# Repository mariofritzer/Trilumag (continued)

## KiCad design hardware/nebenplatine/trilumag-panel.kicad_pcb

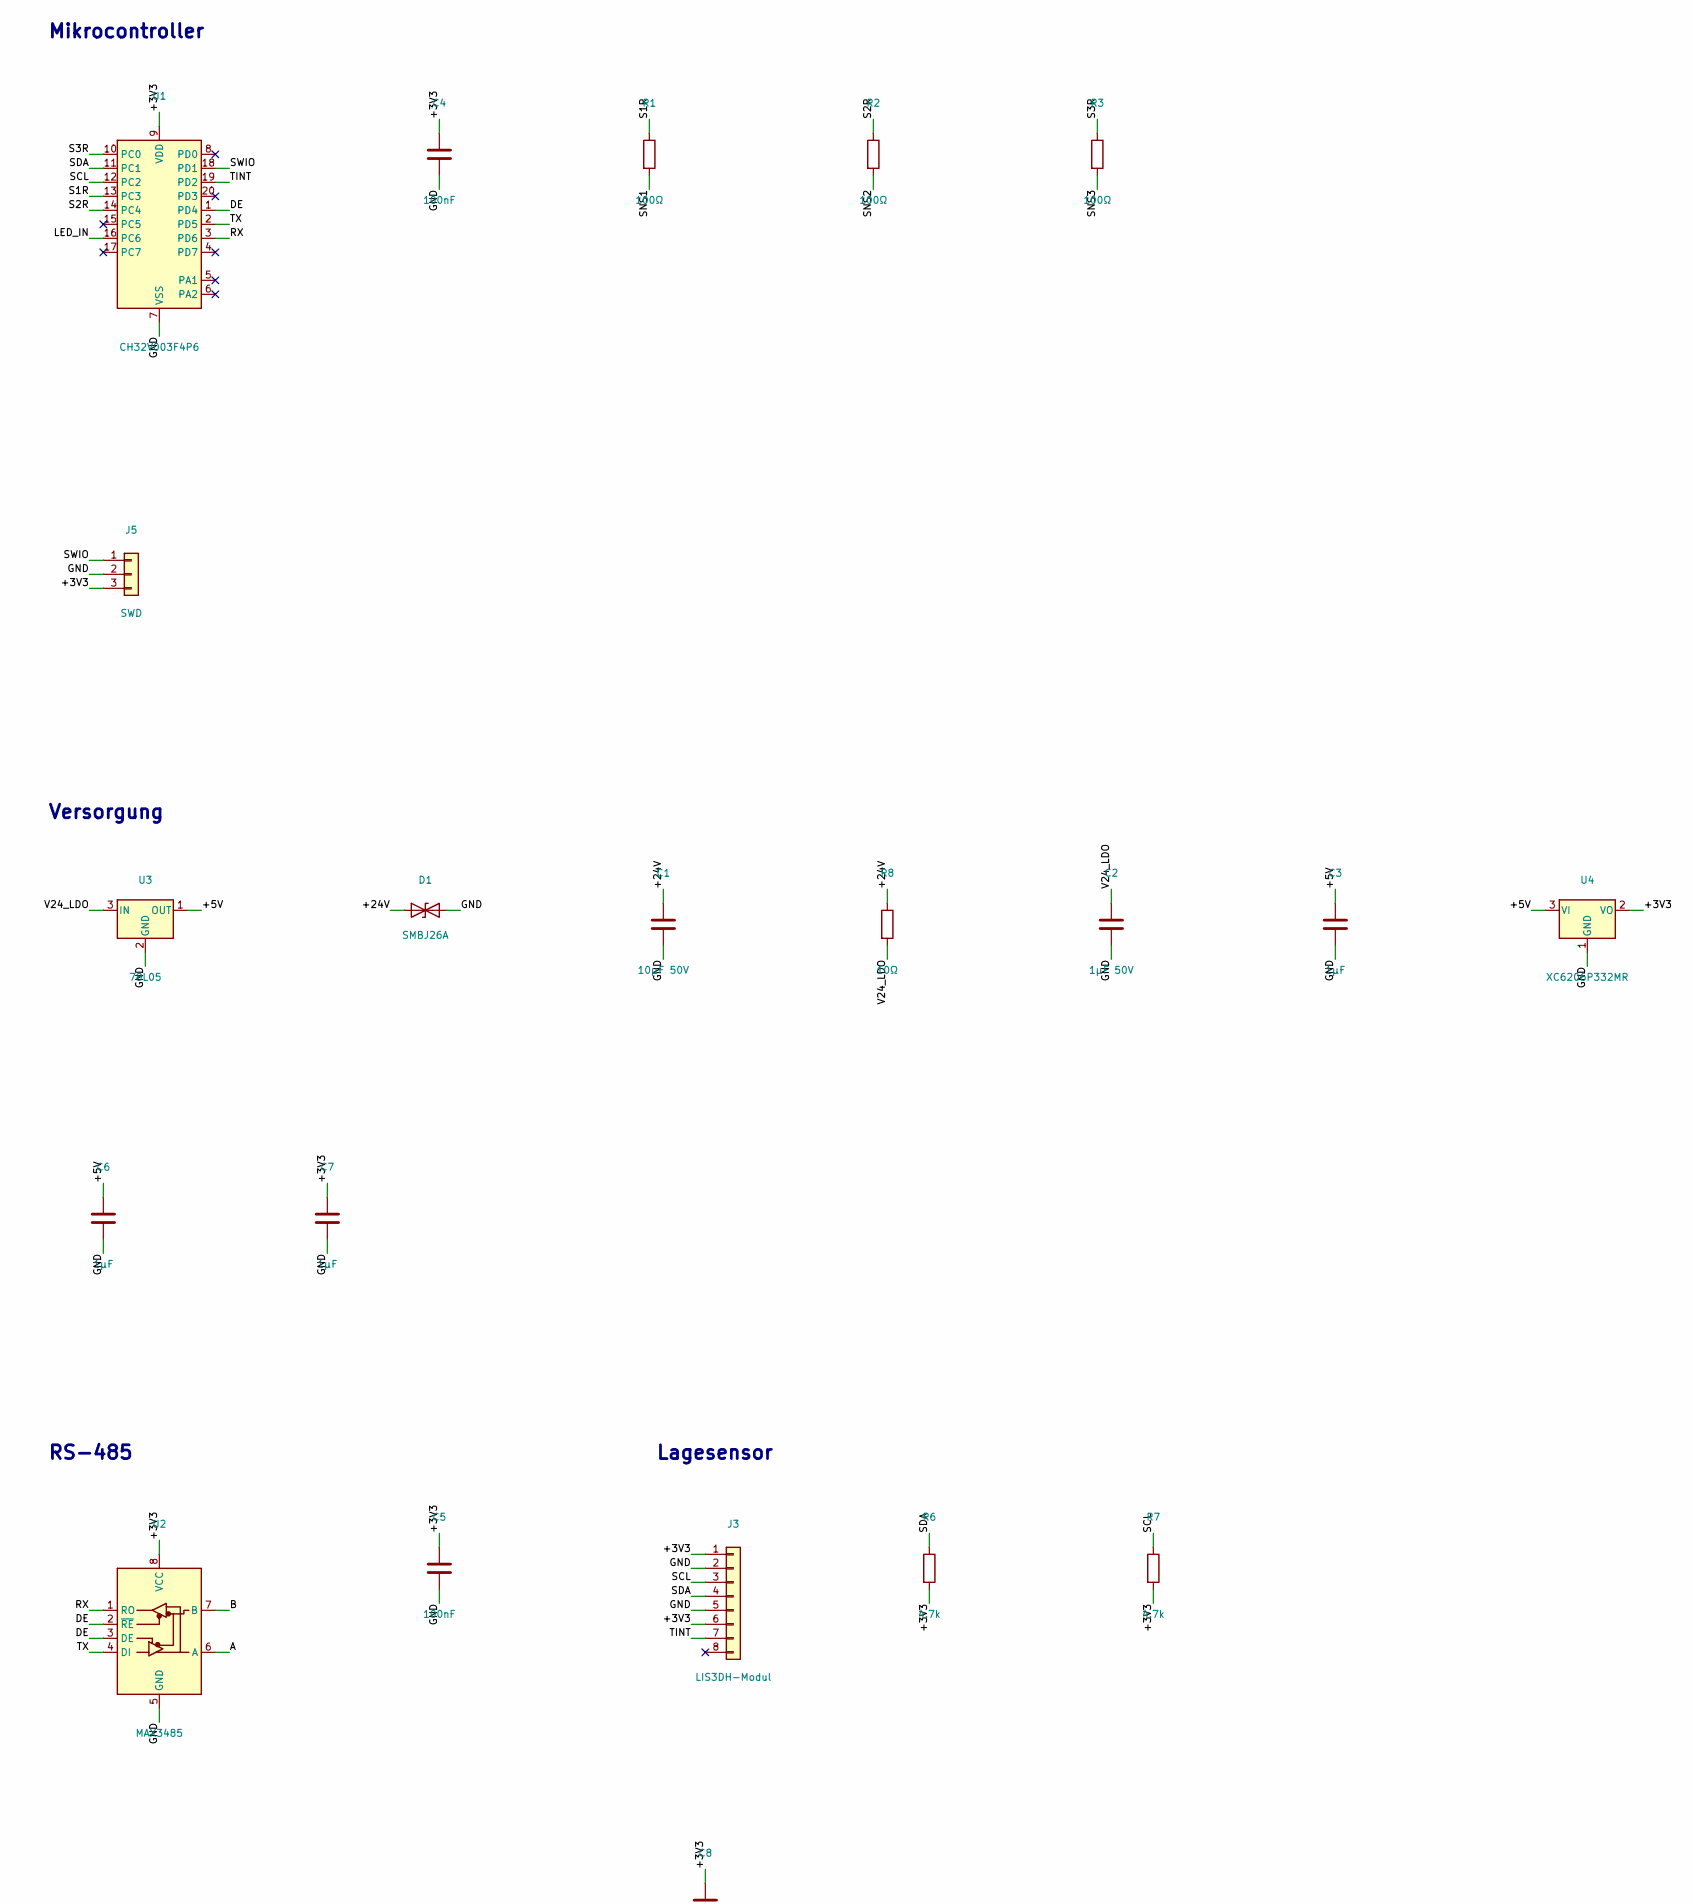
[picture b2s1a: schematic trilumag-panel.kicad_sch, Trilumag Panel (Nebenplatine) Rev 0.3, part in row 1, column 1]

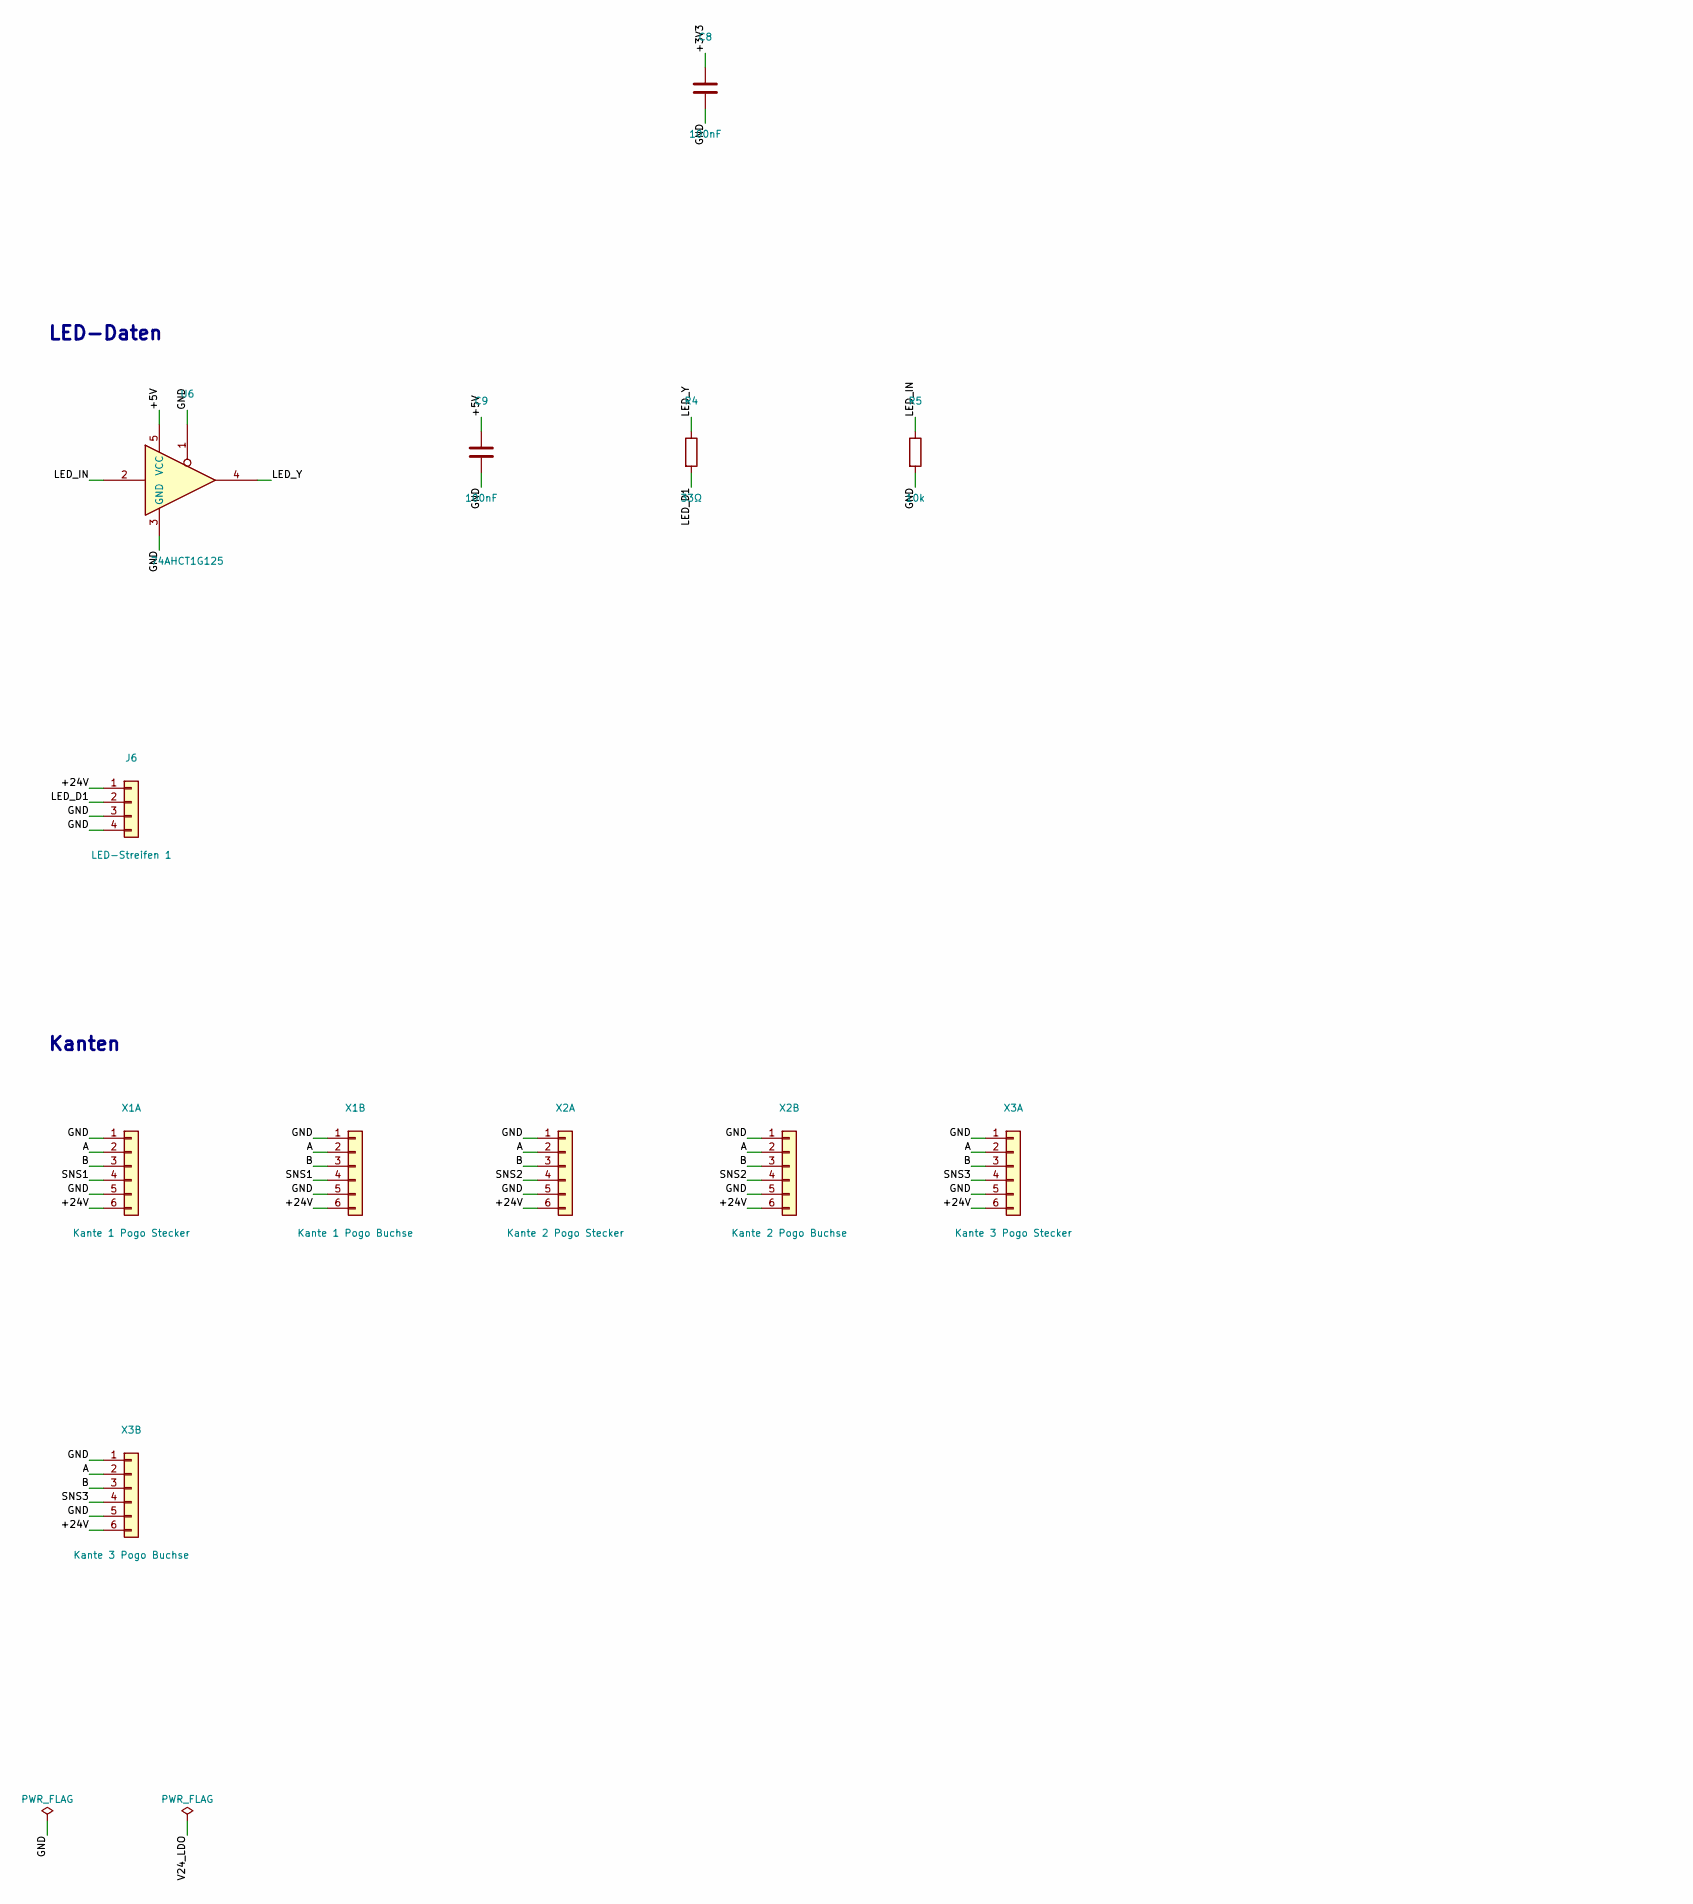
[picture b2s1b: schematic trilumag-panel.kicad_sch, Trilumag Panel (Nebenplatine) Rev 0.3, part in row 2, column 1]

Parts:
C1: 10µF 50V; C_1206_3216Metric_Pad1.33x1.80mm_HandSolder
C2: 1µF 50V; C_0805_2012Metric_Pad1.18x1.45mm_HandSolder
C3, C6, C7: 1µF; C_0805_2012Metric_Pad1.18x1.45mm_HandSolder
C4, C5, C8, C9: 100nF; C_0805_2012Metric_Pad1.18x1.45mm_HandSolder
D1: SMBJ26A; D_SMB_Handsoldering
J3: LIS3DH-Modul; PinSocket_1x08_P2.54mm_Vertical
J5: SWD; PinHeader_1x03_P2.54mm_Vertical
J6: LED-Streifen 1; Kabel_4P_LED
R1, R2, R3: 100Ω; R_0805_2012Metric_Pad1.20x1.40mm_HandSolder
R4: 33Ω; R_0805_2012Metric_Pad1.20x1.40mm_HandSolder
R5: 10k; R_0805_2012Metric_Pad1.20x1.40mm_HandSolder
R6, R7: 4.7k; R_0805_2012Metric_Pad1.20x1.40mm_HandSolder
R8: 10Ω; R_1206_3216Metric_Pad1.30x1.75mm_HandSolder
U1: CH32V003F4P6; TSSOP-20_4.4x6.5mm_P0.65mm
U2: MAX3485; SOIC-8_3.9x4.9mm_P1.27mm
U3: 78L05; SOT-89-3_Handsoldering
U4: XC6206P332MR; SOT-23_Handsoldering
U6: 74AHCT1G125; SOT-23-5_HandSoldering
X1A: Kante 1 Pogo Stecker; Kabel_6P_Stecker
X1B: Kante 1 Pogo Buchse; Kabel_6P_Buchse
X2A: Kante 2 Pogo Stecker; Kabel_6P_Stecker
X2B: Kante 2 Pogo Buchse; Kabel_6P_Buchse
X3A: Kante 3 Pogo Stecker; Kabel_6P_Stecker
X3B: Kante 3 Pogo Buchse; Kabel_6P_Buchse

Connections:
+3V3: C4.1, C5.1, C7.1, C8.1, J3.1, J3.6, J5.3, R6.2, R7.2, U1.9 (VDD), U2.8 (VCC), U4.2 (VO)
+5V: C3.1, C6.1, C9.1, U3.1 (OUT), U4.3 (VI), U6.5 (VCC)
+24V: C1.1, D1.1 (A1), J6.1, R8.1, X1A.6, X1B.6, X2A.6, X2B.6, X3A.6, X3B.6
A: U2.6 (A), X1A.2, X1B.2, X2A.2, X2B.2, X3A.2, X3B.2
B: U2.7 (B), X1A.3, X1B.3, X2A.3, X2B.3, X3A.3, X3B.3
DE: U1.1 (PD4), U2.2 (~RE), U2.3 (DE)
GND: C1.2, C2.2, C3.2, C4.2, C5.2, C6.2, C7.2, C8.2, C9.2, D1.2 (A2), J3.2, J3.5, J5.2, J6.3, J6.4, R5.2, U1.7 (VSS), U2.5 (GND), U3.2 (GND), U4.1 (GND), U6.1, U6.3 (GND), X1A.1, X1A.5, X1B.1, X1B.5, X2A.1, X2A.5, X2B.1, X2B.5, X3A.1, X3A.5, X3B.1, X3B.5; also elsewhere on the board
LED_D1: J6.2, R4.2
LED_IN: R5.1, U1.16 (PC6), U6.2
LED_Y: R4.1, U6.4
RX: U1.3 (PD6), U2.1 (RO)
S1R: R1.1, U1.13 (PC3)
S2R: R2.1, U1.14 (PC4)
S3R: R3.1, U1.10 (PC0)
SCL: J3.3, R7.1, U1.12 (PC2)
SDA: J3.4, R6.1, U1.11 (PC1)
SNS1: R1.2, X1A.4, X1B.4
SNS2: R2.2, X2A.4, X2B.4
SNS3: R3.2, X3A.4, X3B.4
SWIO: J5.1, U1.18 (PD1)
TINT: J3.7, U1.19 (PD2)
TX: U1.2 (PD5), U2.4 (DI)
V24_LDO: C2.1, R8.2, U3.3 (IN)

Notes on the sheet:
Mikrocontroller
Versorgung
RS-485
Lagesensor
LED-Daten
Kanten

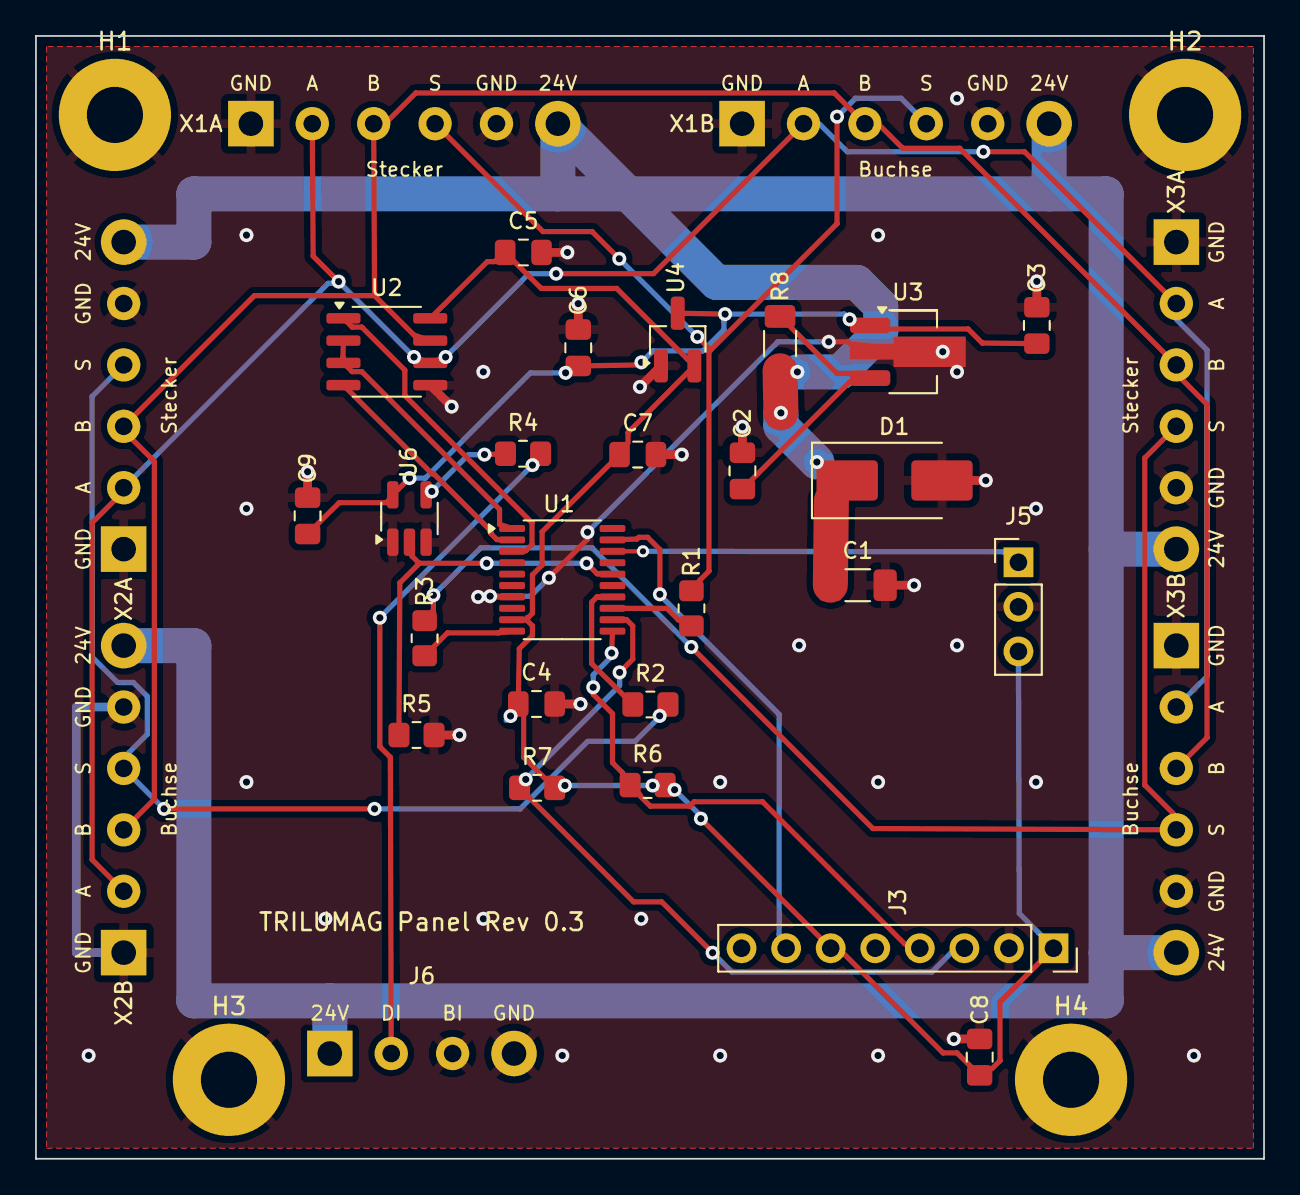
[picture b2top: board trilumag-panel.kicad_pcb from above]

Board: 2 copper layers, 70.0 x 64.0 mm, 36 parts (0 on the bottom side), 23 nets.

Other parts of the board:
H1, H2, H3, H4: M3; MountingHole_3.2mm_M3_Pad

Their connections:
GND: H1.1, H2.1, H3.1, H4.1; also elsewhere on the board

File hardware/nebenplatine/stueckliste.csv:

Menge;Referenzen;Wert;Footprint;Bestellhinweis
1;C1;10µF 50V;C_1206_3216Metric_Pad1.33x1.80mm_HandSolder;X5R/X7R 1206 50 V
1;C2;1µF 50V;C_0805_2012Metric_Pad1.18x1.45mm_HandSolder;
3;C3 C6 C7;1µF;C_0805_2012Metric_Pad1.18x1.45mm_HandSolder;
4;C4 C5 C8 C9;100nF;C_0805_2012Metric_Pad1.18x1.45mm_HandSolder;
1;D1;SMBJ26A;D_SMB_Handsoldering;SMBJ26A
1;J3;LIS3DH-Modul;PinSocket_1x08_P2.54mm_Vertical;
1;J5;SWD;PinHeader_1x03_P2.54mm_Vertical;
1;J6;LED-Streifen 1;Kabel_4P_LED;
3;R1 R2 R3;100Ω;R_0805_2012Metric_Pad1.20x1.40mm_HandSolder;
1;R4;33Ω;R_0805_2012Metric_Pad1.20x1.40mm_HandSolder;
1;R5;10k;R_0805_2012Metric_Pad1.20x1.40mm_HandSolder;
2;R6 R7;4.7k;R_0805_2012Metric_Pad1.20x1.40mm_HandSolder;
1;R8;10Ω;R_1206_3216Metric_Pad1.30x1.75mm_HandSolder;
1;U1;CH32V003F4P6;TSSOP-20_4.4x6.5mm_P0.65mm;CH32V003F4P6
1;U2;MAX3485;SOIC-8_3.9x4.9mm_P1.27mm;MAX3485ESA / SP3485EN
1;U3;78L05;SOT-89-3_Handsoldering;78L05 SOT-89 (≥30 V Eingang)
1;U4;XC6206P332MR;SOT-23_Handsoldering;XC6206P332MR (3,3 V)
1;U6;74AHCT1G125;SOT-23-5_HandSoldering;74AHCT1G125 SOT-23-5
1;X1A;Kante 1 Pogo Stecker;Kabel_6P_Stecker;Magnet-Pogo 6-pol. männlich
1;X1B;Kante 1 Pogo Buchse;Kabel_6P_Buchse;Magnet-Pogo 6-pol. weiblich
1;X2A;Kante 2 Pogo Stecker;Kabel_6P_Stecker;Magnet-Pogo 6-pol. männlich
1;X2B;Kante 2 Pogo Buchse;Kabel_6P_Buchse;Magnet-Pogo 6-pol. weiblich
1;X3A;Kante 3 Pogo Stecker;Kabel_6P_Stecker;Magnet-Pogo 6-pol. männlich
1;X3B;Kante 3 Pogo Buchse;Kabel_6P_Buchse;Magnet-Pogo 6-pol. weiblich

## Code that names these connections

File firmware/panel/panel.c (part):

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  Gebaut mit ch32fun (https://github.com/cnlohr/ch32fun).

  Pins (CH32V003F4P6):
    PD5  USART1 TX  -> MAX485 DI
    PD6  USART1 RX  <- MAX485 RO
    PD4  Senderichtung -> MAX485 DE und /RE
    PC3  SNS Kante 1 (über 100 Ohm)
    PC4  SNS Kante 2
    PC0  SNS Kante 3
    PC1  I2C SDA  -> Beschleunigungssensor LIS2DH12 (Touch)
    PC2  I2C SCL  -> LIS2DH12
    PD2  INT1 vom LIS2DH12 (High = Antippen erkannt)
    PC6  LED-Daten (SPI MOSI) -> WS2814, Kette Kante 1, 2, 3
    PD1  SWIO zum Programmieren

  Verhalten: startet dunkel und ohne Adresse, wird vom Hauptpanel gefunden,
  pulsiert dann blau, bis die erste Farbe kommt. Protokoll: docs/protokoll.md
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
static void uartInit(void) {
	RCC->APB2PCENR |= RCC_APB2Periph_GPIOD | RCC_APB2Periph_USART1 | RCC_APB2Periph_AFIO;
	funPinMode(PD5, GPIO_CFGLR_OUT_10Mhz_AF_PP);
	funPinMode(PD6, GPIO_CFGLR_IN_PUPD);
	funDigitalWrite(PD6, FUN_HIGH);
	funPinMode(PD4, GPIO_CFGLR_OUT_10Mhz_PP);
	funDigitalWrite(PD4, FUN_LOW);
	USART1->BRR = FUNCONF_SYSTEM_CORE_CLOCK / BAUD;
	USART1->CTLR1 = USART_CTLR1_UE | USART_CTLR1_TE | USART_CTLR1_RE | USART_CTLR1_RXNEIE;
	NVIC_EnableIRQ(USART1_IRQn);
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
static void sendFrame(uint8_t addr, uint8_t cmd, const uint8_t* data, uint8_t len) {
	uint8_t c = 0;
	funDigitalWrite(PD4, FUN_HIGH);
	Delay_Us(5);
	const uint8_t head[4] = {SYNC, addr, cmd, len};
	for (int i = 0; i < 4; i++) {
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	while (!(USART1->STATR & USART_STATR_TXE));
	USART1->DATAR = c;
	while (!(USART1->STATR & USART_STATR_TC));
	funDigitalWrite(PD4, FUN_LOW);
}

static void reply(uint8_t cmd, const uint8_t* data, uint8_t len) {
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}

// ---------- SNS-Leitungen ----------
static const uint8_t snsPin[3] = {PC3, PC4, PC0};

static void snsApply(void) {
	for (int e = 0; e < 3; e++) {
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static void i2cInit(void) {
	RCC->APB2PCENR |= RCC_APB2Periph_GPIOC | RCC_APB2Periph_GPIOD | RCC_APB2Periph_AFIO;
	RCC->APB1PCENR |= RCC_APB1Periph_I2C1;
	funPinMode(PC1, GPIO_CFGLR_OUT_10Mhz_AF_OD);   // SDA
	funPinMode(PC2, GPIO_CFGLR_OUT_10Mhz_AF_OD);   // SCL
	funPinMode(PD2, GPIO_CFGLR_IN_FLOAT);        // INT1, der Sensor treibt aktiv
	RCC->APB1PRSTR |= RCC_APB1Periph_I2C1;
	RCC->APB1PRSTR &= ~RCC_APB1Periph_I2C1;
	I2C1->CTLR2 = (FUNCONF_SYSTEM_CORE_CLOCK / 1000000) & I2C_CTLR2_FREQ;
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	for (uint32_t t = 0; t < 20000; t++) if (I2C1->STAR1 & I2C_STAR1_RXNE) return (uint8_t)I2C1->DATAR;
	return -1;
}
#define accIntHigh() funDigitalRead(PD2)
#endif

static void touchApply(void) {
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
